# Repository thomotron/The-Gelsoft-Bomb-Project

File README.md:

# The Gelsoft Bomb Project
A [KTANE](https://en.wikipedia.org/wiki/Keep_Talking_and_Nobody_Explodes)-inspired toy bomb for use in [gelsoft](https://en.wikipedia.org/wiki/Gel_ball_shooter) matches.

The core concept is to have a ruggedised case (probably a pistol or camera case like the Pelican Vault V100) that can be opened up to reveal an interactive puzzle and a timer.
If the puzzle is not solved in time, the gelbomb will make a loud beeping noise and stop the timer (sounds lame, but I'm not putting gels in this thing).
This can be incorporated into your own game modes to make things interesting.

The gelbomb It features a highly-modular design, allowing many different puzzle modules to be switched in and out during the course of a day.

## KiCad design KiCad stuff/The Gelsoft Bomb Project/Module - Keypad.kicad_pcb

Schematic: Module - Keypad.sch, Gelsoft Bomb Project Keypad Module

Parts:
J1: ISP; PinHeader_2x03_P2.54mm_Vertical
J2: Module Connector; PinHeader_1x09_P1.27mm_Vertical
R1: 10k; R_Axial_DIN0614_L14.3mm_D5.7mm_P20.32mm_Horizontal
U1: ATmega8-16PU; DIP-28_W7.62mm
U2: 74HC595; DIP-16_W7.62mm
U3: 3x4_Keypad; PinHeader_1x07_P2.54mm_Vertical
U4: MC11605A6W7-BNMLW; PinHeader_1x16_P2.54mm_Vertical

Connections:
5v: J1.1, J2.9, U1.7 (VCC), U2.16 (VCC), U4.2, U4.15
Earth: J1.5, J2.1, J2.2, J2.6, J2.7, R1.2, U1.8 (GND), U2.8 (GND), U4.1
MISO: J1.2, J2.4, U1.18 (PB4)
MOSI: J1.3, J2.3, U1.17 (PB3)
unnamed: R1.1, U4.3
unnamed: U1.2 (PD0), U4.6
unnamed: U1.3 (PD1), U3.3
unnamed: U1.4 (PD2), U3.1
unnamed: U1.5 (PD3), U3.5
unnamed: U1.6 (PD4), U3.2
unnamed: U1.10 (PB7/XTAL2), U2.10 (~SRCLR)
unnamed: U1.11 (PD5), U3.7
unnamed: U1.12 (PD6), U3.6
unnamed: U1.13 (PD7), U3.4
unnamed: U1.23 (PC0), U2.14 (SER)
unnamed: U1.24 (PC1), U2.11 (SRCLK)
unnamed: U1.25 (PC2), U2.12 (RCLK)
unnamed: U1.26 (PC3), U4.16
unnamed: U1.27 (PC4), U4.4
unnamed: U1.28 (PC5), U4.5
unnamed: U2.1 (QB), U4.8
unnamed: U2.2 (QC), U4.9
unnamed: U2.3 (QD), U4.10
unnamed: U2.4 (QE), U4.11
unnamed: U2.5 (QF), U4.12
unnamed: U2.6 (QG), U4.13
unnamed: U2.7 (QH), U4.14
unnamed: U2.15 (QA), U4.7
RESET: J1.6, U1.1 (PC6/~RESET)
SCK: J1.4, J2.5, U1.19 (PB5)
VIN: J2.8

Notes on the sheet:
Keypad
LCD Enable
Shift Reg.
LCD Mode/LED

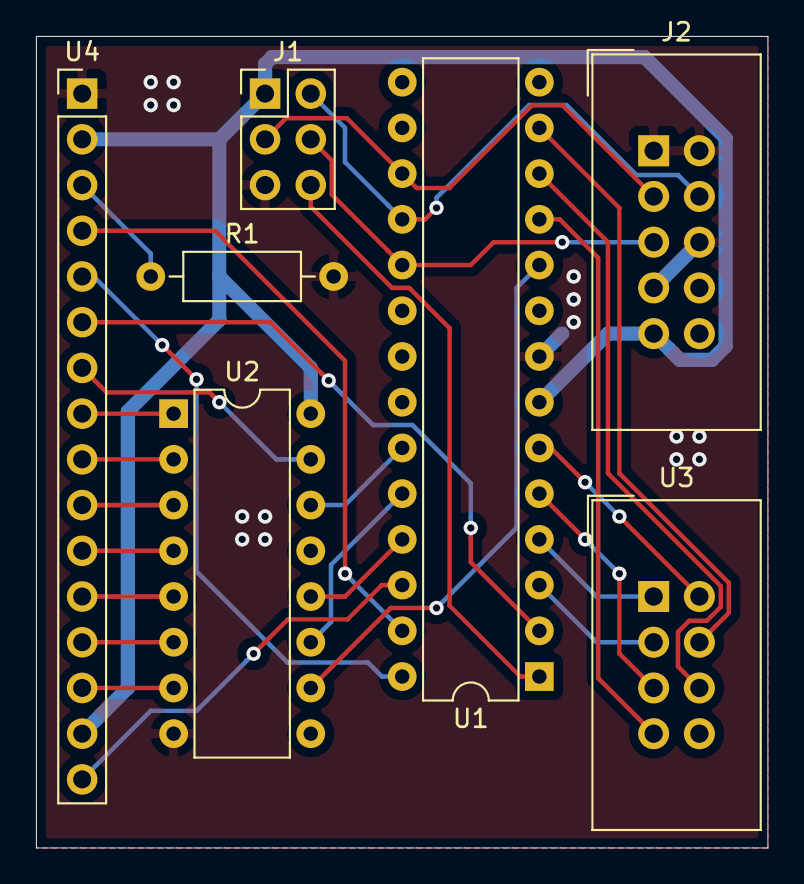
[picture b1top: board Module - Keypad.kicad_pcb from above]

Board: 2 copper layers, 40.6 x 45.1 mm, 7 parts (0 on the bottom side), 30 nets.

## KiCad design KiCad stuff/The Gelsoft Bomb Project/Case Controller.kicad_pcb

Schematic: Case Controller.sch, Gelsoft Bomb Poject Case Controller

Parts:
BZ1: Buzzer; PinHeader_1x02_P2.54mm_Vertical
C1: 470uF; CP_Radial_D10.0mm_P5.00mm
D1: 1N5400; D_DO-201AD_P15.24mm_Horizontal
D2: STRIKE 1; LED_Square_15x15mm
D3: STRIKE 2; LED_Square_15x15mm
J1: ISP; PinHeader_2x03_P2.54mm_Vertical
J2: Module Connector; DSUB-9_Male_Horizontal_P2.77x2.84mm_EdgePinOffset4.94mm_Hou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
J3: Battery Header; PinHeader_1x02_P2.54mm_Vertical
J4: Low-Power Switch; PinHeader_1x02_P2.54mm_Vertical
R1: 20k; R_Axial_DIN0207_L6.3mm_D2.5mm_P10.16mm_Horizontal
R5, R6, R7, R8: 100k; R_Axial_DIN0207_L6.3mm_D2.5mm_P10.16mm_Horizontal
SW1: Power Switch; SK12D07VG3
SW2: PLUS; SW_PUSH_6mm
SW3: MINUS; SW_PUSH_6mm
SW4: OK; SW_PUSH_6mm
U1: Buck_Converter_Module_7-26v; Buck_Converter_Module_7-24v
U2: ATtiny24A-PU; DIP-14_W7.62mm
U3: MAX7219; DIP-24_W7.62mm
U4: HDSP-B09G; HDSP-B08G

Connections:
5v: C1.1, J1.1, J2.9, R1.2, R5.2, SW2.1, SW3.1, SW4.1, U1.3, U2.1, U3.19
BUZZER: BZ1.1, U2.6
Earth: BZ1.2, C1.2, J1.5, J2.1, J2.2, J2.6, J2.7, J3.1, U1.2, U1.4, U2.14, U3.4, U3.9
LOWPOWER: J4.1, U2.13
MINUS: R7.1, U2.11
MISO: J1.2, J2.4, U2.8
MOSI: J1.3, J2.3, U2.7
unnamed: D1.2, SW1.1
unnamed: D2.1, U3.2, U4.12
unnamed: D2.2, D3.2, U3.22, U4.3
unnamed: D3.1, U3.7, U4.6
unnamed: J3.2, SW1.2
unnamed: J4.2, R5.1
unnamed: R1.1, U3.18
unnamed: R6.2, SW2.2
unnamed: R7.2, SW3.2
unnamed: R8.2, SW4.2
unnamed: U2.2, U3.1
unnamed: U2.3, U3.13
unnamed: U2.5, U3.12
unnamed: U3.6, U4.8
unnamed: U3.11, U4.9
unnamed: U3.14, U4.11
unnamed: U3.15, U4.10
unnamed: U3.16, U4.7
unnamed: U3.17, U4.5
unnamed: U3.20, U4.4
unnamed: U3.21, U4.1
unnamed: U3.23, U4.2
OK: R8.1, U2.10
PLUS: R6.1, U2.12
RESET: J1.6, U2.4
SCK: J1.4, J2.5, U2.9
VIN: D1.1, J2.8, U1.1

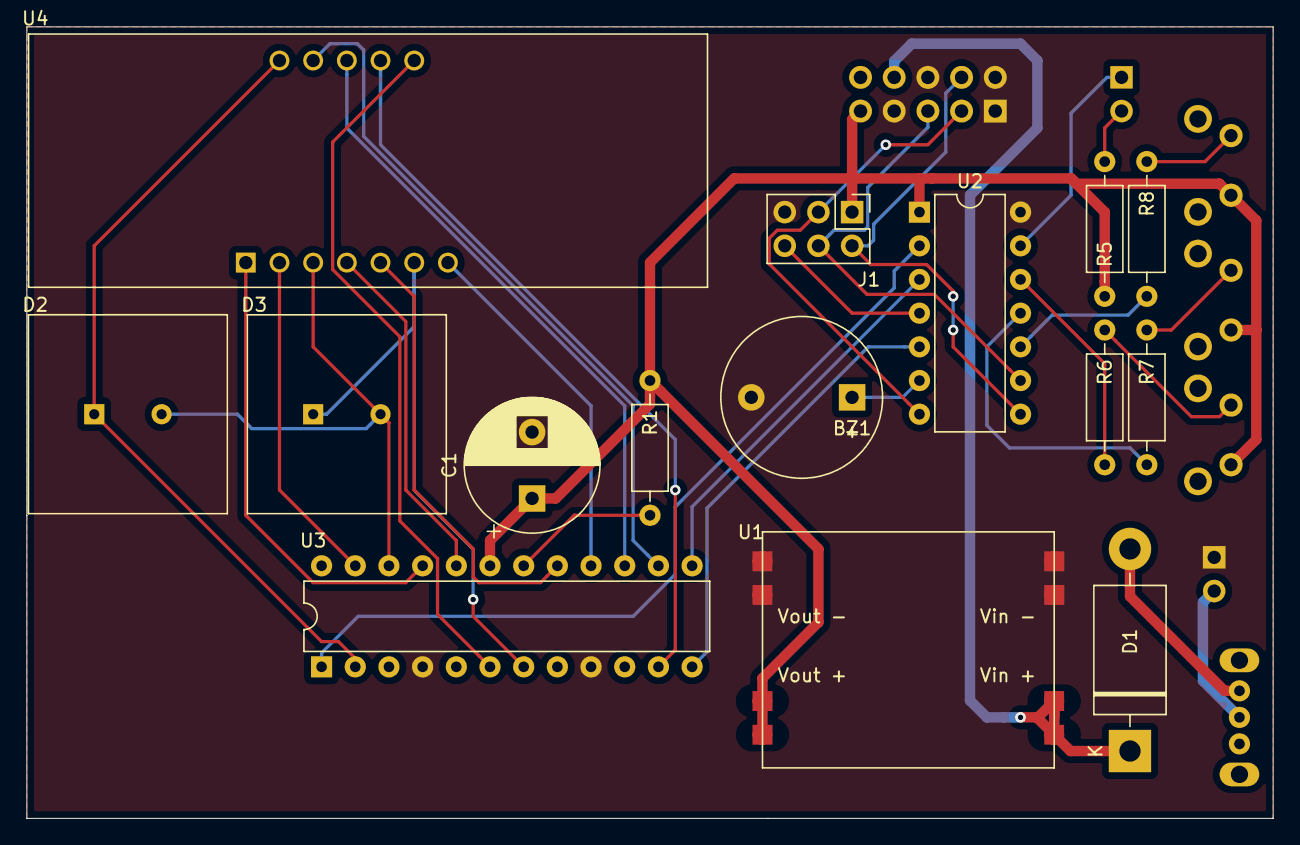
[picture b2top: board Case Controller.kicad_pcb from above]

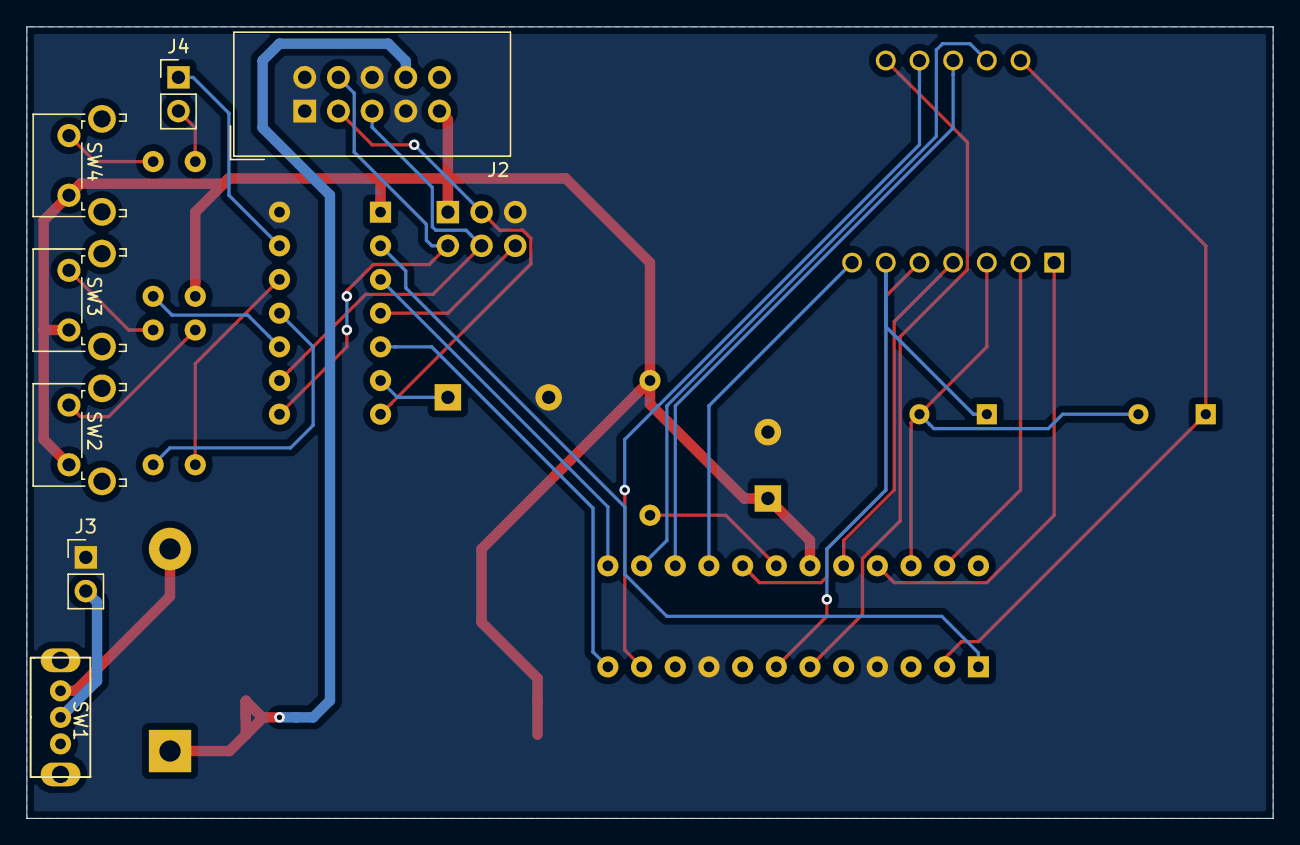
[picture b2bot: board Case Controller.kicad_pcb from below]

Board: 2 copper layers, 94.0 x 59.7 mm, 22 parts (7 on the bottom side), 34 nets.

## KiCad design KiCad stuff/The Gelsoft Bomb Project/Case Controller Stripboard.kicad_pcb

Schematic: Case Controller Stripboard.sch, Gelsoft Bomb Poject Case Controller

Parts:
BZ1: Buzzer; PinHeader_1x02_P2.54mm_Vertical
C1: 100uF; CP_Radial_D6.3mm_P2.50mm
J1: ISP; PinHeader_2x03_P2.54mm_Vertical
J2: Module Connector; DSUB-9_Male_Horizontal_P2.77x2.84mm_EdgePinOffset4.94mm_Hou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
J3: Battery Header; PinHeader_1x02_P2.54mm_Vertical
J4, J5: Conn_01x07; PinSocket_1x07_P2.54mm_Vertical
R1: 20k; R_Axial_DIN0207_L6.3mm_D2.5mm_P10.16mm_Horizontal
U1: L7805; TO-220-4_Vertical
U2: ATtiny24A-PU; DIP-14_W7.62mm
U3: MAX7219; DIP-24_W7.62mm
U4: HDSP-B09G; HDSP-B08G

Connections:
5v: C1.1, J1.1, J2.5, J4.1, R1.2, U1.3, U2.1, U3.19
BUZZER: BZ1.1, J4.6, U2.6
CORRECT: J2.6, J5.6, U2.13
DISARM: J2.8, J5.4, U2.11
GND: BZ1.2, C1.2, J2.1, J3.1, J5.7, U1.2, U2.14, U3.4, U3.9
LOWPOWER: J2.9, J5.3, U2.10
MISO: J5.1, U2.8
MOSI: J4.7, U2.7
unnamed: R1.1, U3.18
unnamed: U3.2, U4.12
unnamed: U3.6, U4.8
unnamed: U3.7, U4.6
unnamed: U3.11, U4.9
unnamed: U3.14, U4.11
unnamed: U3.15, U4.10
unnamed: U3.16, U4.7
unnamed: U3.17, U4.5
unnamed: U3.20, U4.4
unnamed: U3.21, U4.1
unnamed: U3.22, U4.3
unnamed: U3.23, U4.2
Pin2: J4.2, U2.2, U3.1
Pin3: J4.3, U2.3, U3.13
Pin5: J4.5, U2.5, U3.12
RESET: J4.4, U2.4
SCK: J5.2, U2.9
STRIKE: J2.7, J5.5, U2.12
VIN: J2.4, J3.2, U1.1

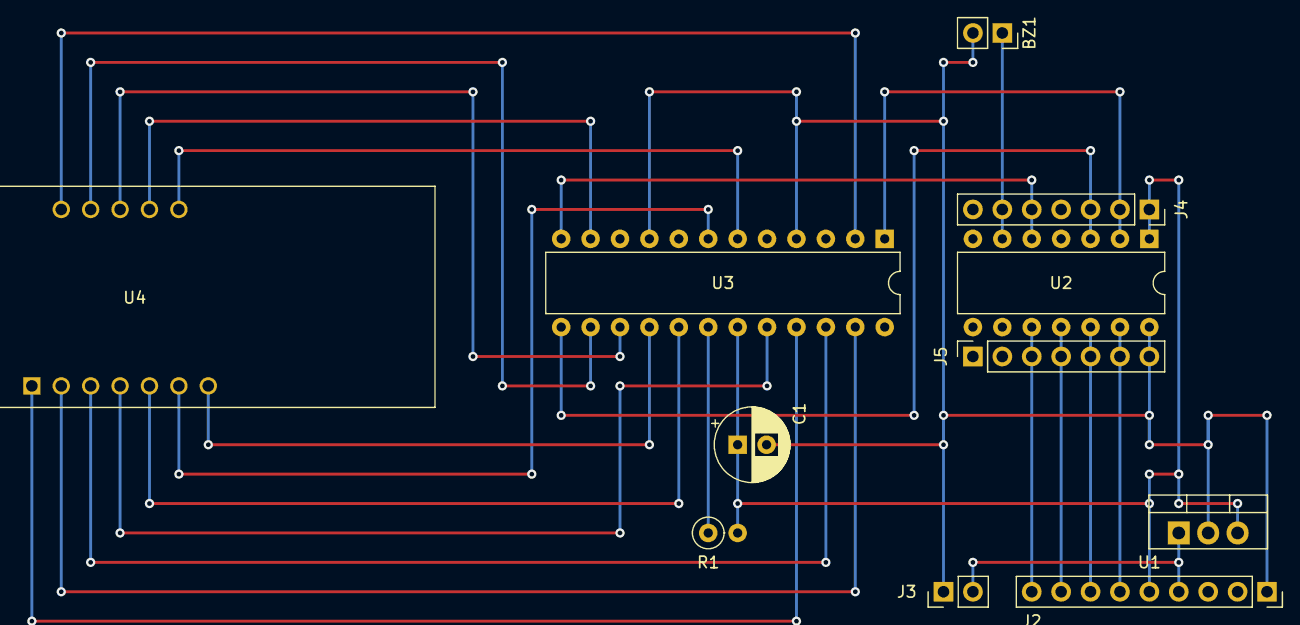
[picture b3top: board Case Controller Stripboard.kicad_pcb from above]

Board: 2 copper layers, 11 parts (0 on the bottom side), 28 nets.

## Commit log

2019-09-06 Add Arduino sketches
2019-09-06 Add KiCad files
2019-09-07 Add Makefile
2019-09-07 Rename .ino to .c and fix indentation
2019-09-07 WIP: Add initial schematic
2019-09-07 Use a demuxer and a single latch for simplicity
2019-09-08 Add and use HT16K33
2019-09-08 Add and use MAX7219
    Chips ahoy!
    Finally found the one we should be using. The 7219 supports up to 8 digits *including* decimal places *and* it uses a shift register with latches and current sourcing/sinking built in! It's the perfe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
2019-09-08 Downgrade MCU to an ATTiny24A
    We don't need all of the extra features on a Mega328P, the Tiny24A should do it just fine
2019-09-08 Add RS232 connector and finalise schematic
2019-09-08 Add battery connector
2019-09-08 Add VIN to module connector
    Should be more flexible if modules want to draw more juice or supply some extra
2019-09-08 Annotate case controller schematic
2019-09-08 Associate footprints with each component
2019-09-08 Create first case controller PCB prototype
2019-09-08 Move vias
2019-09-08 Rename project files
2019-09-08 Add pinout comment to top of file
    Man that'll come in *very* handy later on
2019-09-09 Rework case controller code for avr-libc and avr-gcc
2019-09-09 Make the project properly
2019-09-09 Add clean target
2019-09-09 Add serial functions and finish writeDigit functionality
2019-09-09 Handle interrupts
2019-09-09 Restructure main function
2019-09-09 Update function prototypes
2019-09-09 Use Allman style, damnit
2019-09-09 Add custom digit struct and replace arrays in writeDigits function
2019-09-09 Add flash and fuse make targets
2019-09-09 Ignore compilation artifacts
2019-09-10 Use MAX7219 library and implement LED countdown
2019-09-10 Remove pullups
2019-09-10 Tweak finish conditions and blink display
2019-09-10 Optimise if conditions
2019-09-10 Set direction registers
2019-09-10 Decrease display test length to one second
2019-09-10 Add buzzer to countdown
2019-09-16 Add keypad module schematic and parts
2019-09-16 Add initial code for keypad module
2019-10-12 Finalise the keypad module and add a PCB design
2019-10-12 Add labels to pins and draw logical groups
2019-10-12 Add keypad logic
2019-10-13 Add a new LCD and replace the old one
2019-10-13 Ignore KiCad backups
2019-10-13 WIP: Add LCD and shift register classes
2019-10-13 Update gitignore to include -bak extensions
2019-10-13 Remove that one backup that I really didn't want to commit
2019-10-13 Change byte macro due to some weird overlap
2019-10-13 Fix compiler variable array declaration complaint
    Turns out that 'const' is equivalent to read-only, not actually constant, so the compile has a cry about initialising arrays with consts.
2019-10-13 Fix a variety of compiler issues
2019-10-13 Rename ser_clock to sgift_clock
2019-10-13 Add write methods for the shift register and LCD
2019-10-13 Ignore .idea
2019-10-13 Add LCD command functionality
2019-10-13 Add comments for command functions
2019-10-13 Move prototypes into header file
2019-10-13 Ignore CMake build directories
2019-10-13 Add newline to end of file
2019-10-13 Add CMakeLists.txt to make CLion happy
    Still using the Makefile to actually compile and flash. I just want good syntax highlighting, code completion, and error checking.
2019-10-13 Added LCD write functions
2019-10-13 Privatised most LCD functions
    They shouldn't be accessed directly, especially since they're pretty much direct to RAM
2019-11-02 Optimise code size when compiling
2019-11-02 Show program size when compiling
2019-11-02 Add clock frequency variable to Makefile
2019-11-02 Fix issue where some digits would not illuminate
    Turns out the library was wrong, it was shifting by the digit number instead of using the number in BCD (i.e. digit 3 is 0011)
2019-11-02 Reverse < condition
2019-11-02 Invert digit order
2019-11-02 Ignore CLion artifacts
2019-11-02 Add CMake config
2019-11-02 Add missing prototype
2019-11-02 Add support for decimal points
2019-11-02 Expand 7-segment font
2019-11-02 Move display update into its own function
2019-11-02 Clarify condition
2019-11-02 Add comments
2019-11-02 Actually count down for 5 minutes
2019-11-03 Add explicit beep function
2019-11-03 Refactor main run loop
2019-11-03 Beep for a few seconds when detonating
2019-11-03 Implement a nicer variable-delay system in the main loop
2019-11-03 Re-enable beeping
2019-11-03 Add decoupling cap to the MAX7219
    It makes an unbearable noise on the buzzer if left untreated
2019-11-05 Add CMakeLists for keypad module
2019-11-05 Update Makefile from template
    Now with 100% more compiler optimisations!
2019-11-05 Fix variably-defined array issue
    Arrays like to be compile-time constant, so use a define instead
2019-11-05 Add missing semicolon
2019-11-05 Use correct pin variable
2019-11-05 Add gitignore
2019-11-05 Loop forever after breaking out of the MRL
2019-11-24 Board tweaks
2019-11-24 Clean up code a bit
2019-11-24 Add stripboard adaptation of the case controller circuit
2019-11-28 Revise case controller
    Added a buck converter for more efficient power regulation
    Added a diode to the battery for safety
    Added a power switch
    Reworked the PCB design to suit these upgrades
2019-11-28 Ignore caches
2019-11-29 Add v0.1.0 board screenshots
2019-11-29 Use GitHub gitignore and add project lib references
    Removing the lib tables was a mistake, they're actually for including project-level libraries. Besides, this gitignore is more robust and official anyway.
2019-12-01 Add an API doc for the core serial interface
2019-12-01 Overhaul into v0.2.0 (see desc)
    Added buttons to set the timer
    Added the low-power switch
    Added strike LEDs (2 for now, since we don't want another LED driver)
2019-12-01 Replace buck converter with a pre-made module
    Bugger having to deal with making my own, we'll just keep things simple and cheap
2019-12-03 Add fab layer outlines
2019-12-03 Update footprints and use new layout
2019-12-04 Allow pads to be connected to fill zones
2019-12-04 Route PCB
2019-12-05 Update keypad with new connector pinout
2019-12-05 Revise PCB for new pinout
2019-12-05 Use better footprints
2019-12-09 WIP: serial
2019-12-10 Add the button-press time setting mechanism
    Not working on the micro for some reason, might need to invesitgate port direction
2019-12-10 Remove header
2019-12-28 Actually read from the INPUT register and not the OUTPUT register
    Silly dum dum
2019-12-28 Rework time setting and extract into its own function
2019-12-28 Remove redundant function
2019-12-28 Make blinking logic more accessible
    Individual digits can now be toggled for blinking and the blink function is callable from different display update functions
2019-12-29 Add Low Power flag
2019-12-29 Remove volatility from state vars
2019-12-29 Move digit break condition into while
2019-12-29 Remove redundant pressed check
2019-12-29 Add more dynamic blinking logic
    Everything needed for blinking is held in the blinkSettings struct, which is referenced by the doDisplayBlink() function.
    Additionally, blinking is based on cycles now, so that timing can be altered for greater responsiveness in the background while keeping the display consistent.
